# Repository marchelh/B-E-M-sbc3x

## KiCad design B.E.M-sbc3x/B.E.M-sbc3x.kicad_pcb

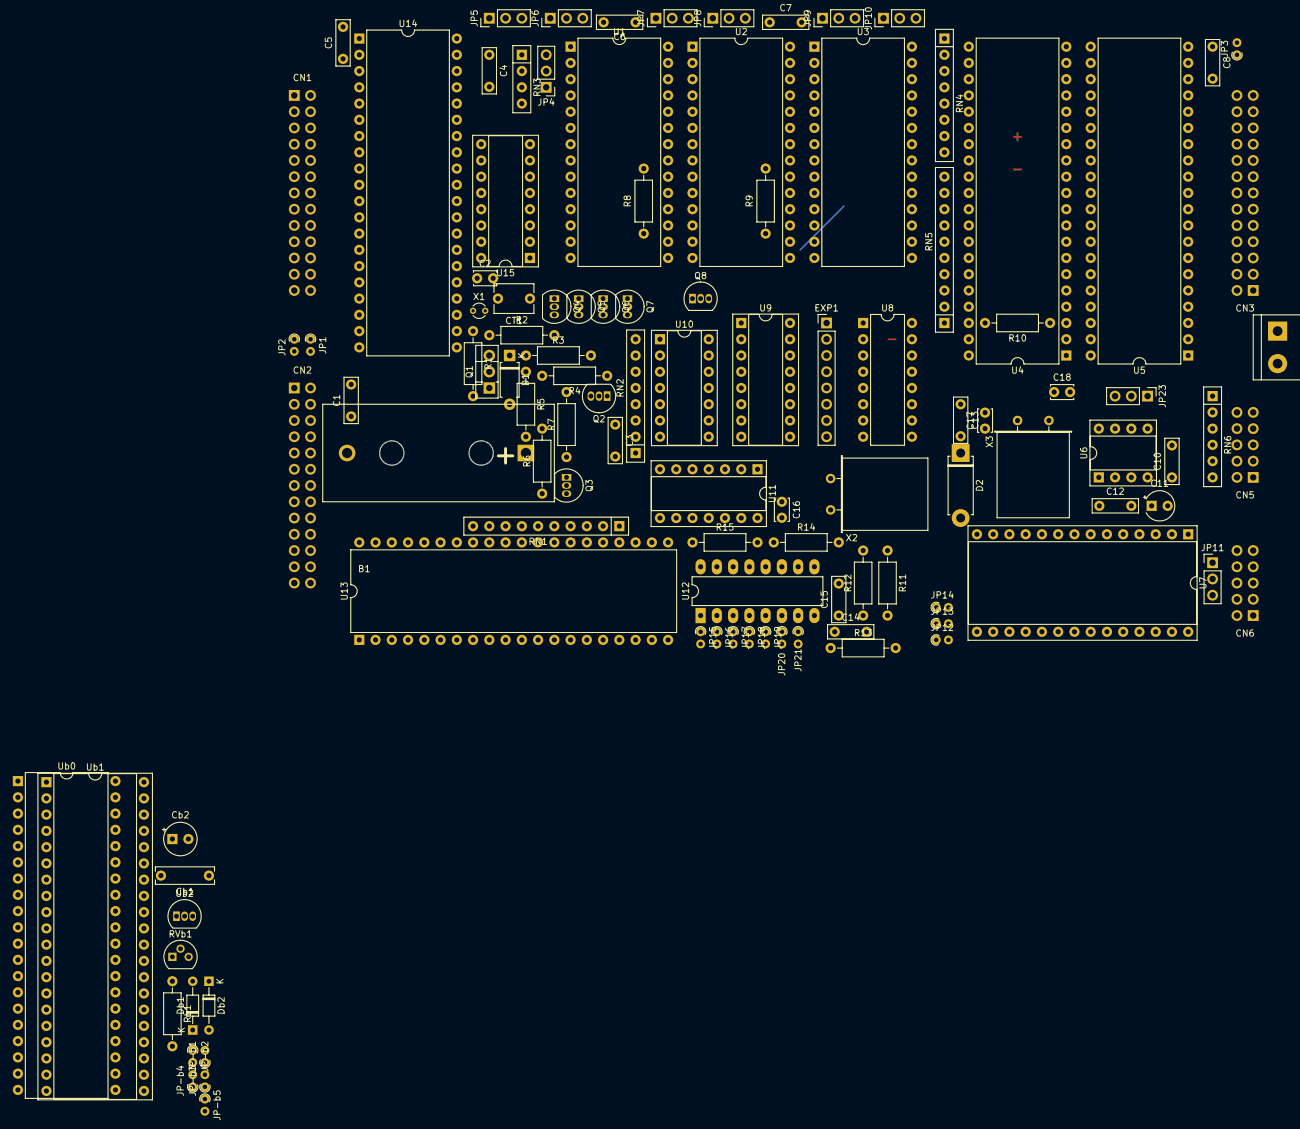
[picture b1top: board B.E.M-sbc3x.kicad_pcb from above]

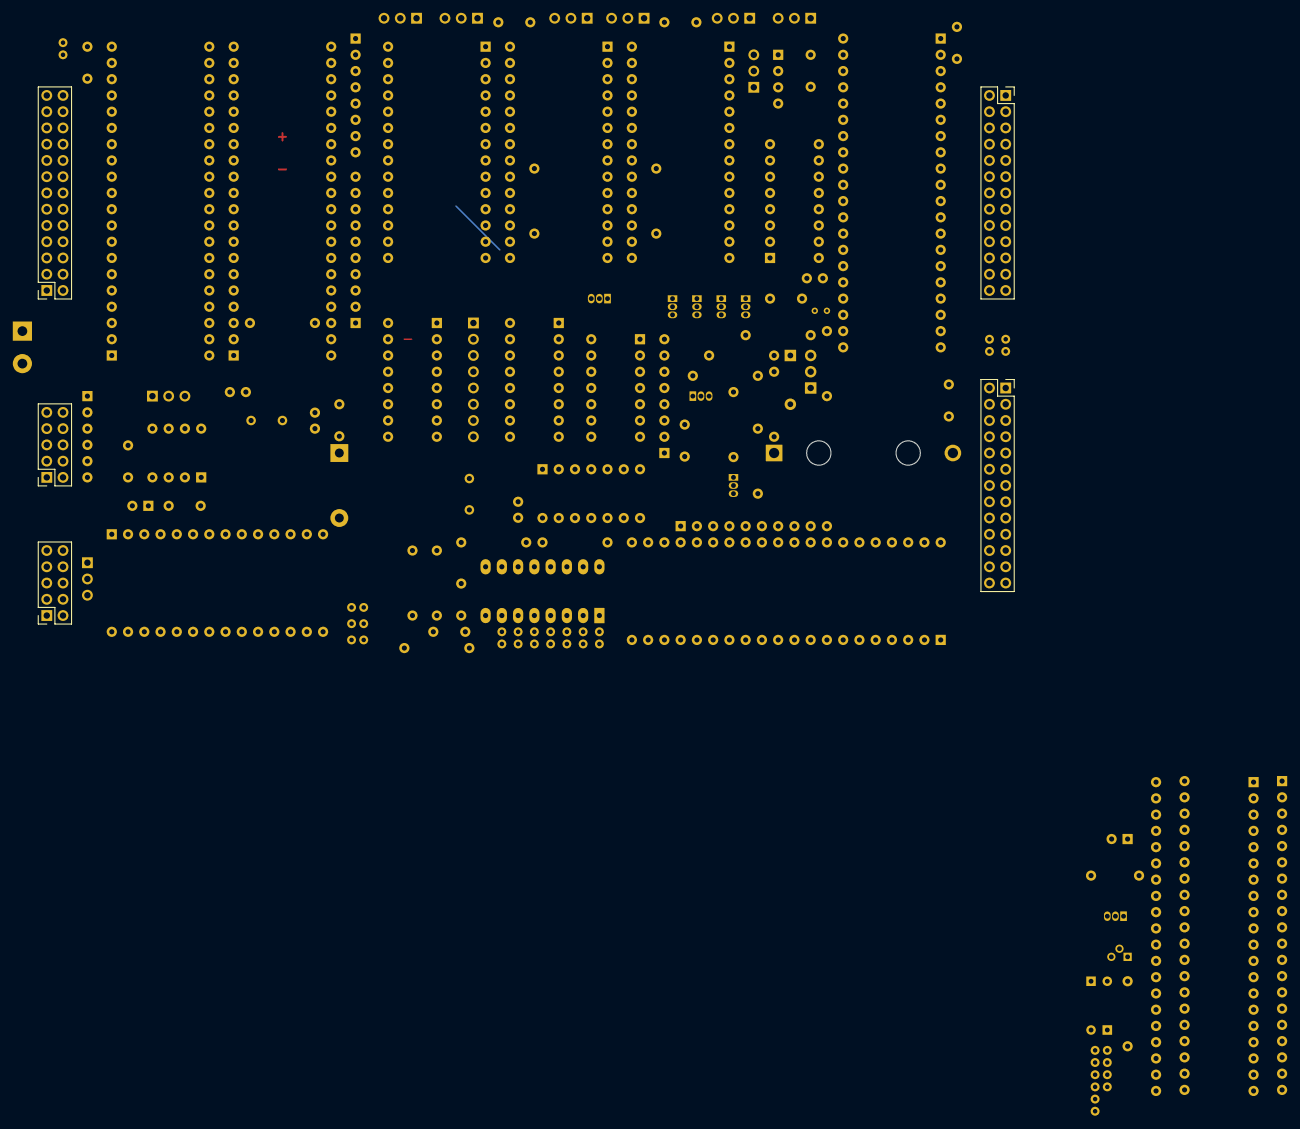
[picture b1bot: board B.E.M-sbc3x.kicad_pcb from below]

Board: 2 copper layers, 111 parts (5 on the bottom side), 206 nets.

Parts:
B1: Battery_Cell; Battery_3.6v
C1, C3, C4, C5, C6, C7, C8, C10, C12, C13, C14, C15: 100nF; C_Rect_L7.0mm_W2.0mm_P5.00mm
C2, C17, C18: 22pF; C_Disc_D3.4mm_W2.1mm_P2.50mm
C11: 10uF; CP_Radial_Tantal_D4.5mm_P2.50mm
C16: 100pF; C_Disc_D3.4mm_W2.1mm_P2.50mm
CN1, CN2, CN3: Conn_02x13_Odd_Even; PinSocket_2x13_P2.54mm_Vertical
CN5, CN6: Conn_02x05_Odd_Even; PinSocket_2x05_P2.54mm_Vertical
CT1: 6-30pF; C_Disc_D6.0mm_W4.4mm_P5.00mm
Cb1: 100nF; C_Rect_L9.0mm_W2.5mm_P7.50mm_MKT
Cb2: 100pF; CP_Radial_Tantal_D5.0mm_P2.50mm
D1: 1N4148; D_A-405_P7.62mm_Horizontal
D2: 1N4148; D_5W_P10.16mm_Horizontal
Db1, Db2: 1n4148; D_DO-34_SOD68_P7.62mm_Horizontal
EXP1: Exp; PinHeader_1x08_P2.54mm_Vertical
J1: Screw_Terminal_01x02; TerminalBlock_bornier-2_P5.08mm
JP1, JP2, JP3, JP12, JP13, JP14, JP15, JP16, JP17, JP18, JP19, JP20, JP21: Jumper_NO_Small; R_Axial_DIN0204_L3.6mm_D1.6mm_P1.90mm_Vertical
JP4, JP5, JP6, JP7, JP8, JP9, JP10, JP11, JP23: Jumper_3_Open; PinHeader_1x03_P2.54mm_Vertical
JP-b1, JP-b2, JP-b3, JP-b4, JP-b5: Device_Jumper_NO_Small; R_Axial_DIN0204_L3.6mm_D1.6mm_P1.90mm_Vertical
Q1: BD136; TO-126-3_Vertical
Q2: BC556; TO-92_Inline
Q3, Q4, Q5, Q6, Q7, Q8: BC547; TO-92_Inline
R1, R3, R4, R13: 10K; R_Axial_DIN0207_L6.3mm_D2.5mm_P10.16mm_Horizontal
R2, R6, R7: 1K; R_Axial_DIN0207_L6.3mm_D2.5mm_P10.16mm_Horizontal
R5: 100; R_Axial_DIN0207_L6.3mm_D2.5mm_P10.16mm_Horizontal
R8, R9, R10, R14, R15: 3.3K; R_Axial_DIN0207_L6.3mm_D2.5mm_P10.16mm_Horizontal
R11: 220K; R_Axial_DIN0207_L6.3mm_D2.5mm_P10.16mm_Horizontal
R12: 22K; R_Axial_DIN0207_L6.3mm_D2.5mm_P10.16mm_Horizontal
RN1, RN5: 10K; R_Array_SIP10
RN2: 2k; R_Array_SIP8
RN3: 3.3K; R_Array_SIP4
RN4: 10K; R_Array_SIP8
RN6: 3.3K; R_Array_SIP6
RVb1: R_POT; TO-92
Rb1: 2.2K; R_Axial_DIN0207_L6.3mm_D2.5mm_P10.16mm_Horizontal
U1, U2: TC55257PL-12; DIP-28_W15.24mm
U3: 27256; DIP-28_W15.24mm
U4: MC68A09; DIP-40_W15.24mm
U5, U13, U14: 6822; DIP-40_W15.24mm
U6: TL7705ACPSR; DIP-8_W7.62mm_Socket
U7: INS2651; DIP-28_W15.24mm_Socket
U8: DM74S571; DIP-16_W7.62mm
U9: 74LS42; DIP-16_W7.62mm_Socket
U10: 74LS00; DIP-14_W7.62mm_Socket
U11: 74HC04; DIP-14_W7.62mm_Socket
U12: CD4060BCN; DIP-16_W7.62mm_LongPads
U15: MM58274BN; DIP-16_W7.62mm_Socket
Ub0: 6822; DIP-40_W15.24mm
Ub1: HD46508PA; DIP-40_W15.24mm_Socket
Ub2: LM336; TO-92_Inline
X1: 32.768; Crystal_DS26_D2.0mm_L6.0mm_Vertical
X2: 5.0688; Crystal_HC18-U_Horizontal
X3: 4.000; Crystal_HC18-U_Horizontal

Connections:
+5C: Cb1.1, Cb2.1, JP-b1.2, Rb1.2, Ub0.20, Ub1.20
+5V: C1.2, C3.2, C4.2, C5.2, C6.2, C7.2, C8.2, C10.2, C13.2, C14.2, CN1.1, CN2.1, CN3.1, EXP1.1, J1.1, JP5.3, JP6.3, JP8.3, JP11.2, JP11.3, Q1.1, R7.2, R8.1, R13.1, RN6.1, U3.1, U3.28, U4.7, U4.33, U5.20, U5.24, U6.7, U6.8, U7.26, U8.16, U9.16, U12.16, U13.20, U13.24, U14.20, U14.24
/A0: RN5.6, U1.10, U2.10, U3.10, U4.8, U5.38, U7.12, U13.38, U14.38, U15.12
/A1: RN5.7, U1.9, U2.9, U3.9, U4.9, U5.37, U7.10, U13.37, U14.37, U15.11
/A2: RN5.8, U1.8, U2.8, U3.8, U4.10, U5.36, U13.36, U14.36, U15.10
/A3: RN5.9, U1.7, U2.7, U3.7, U4.11, U5.35, U13.35, U14.35, U15.9
/A4: RN5.10, U1.6, U2.6, U3.6, U4.12
/A5: RN4.8, U1.5, U2.5, U3.5, U4.13
/A6: RN4.7, U1.4, U2.4, U3.4, U4.14
/A7: RN4.5, U1.3, U2.3, U3.3, U4.15
/A8: RN4.6, U1.25, U2.25, U3.25, U4.16, U8.6
/A9: RN4.4, U1.24, U2.24, U3.24, U4.17, U8.7
/A10: RN4.2, RN5.5, U1.21, U2.21, U3.21, U4.18, U8.4
/A11: JP4.1, JP4.2, JP6.1, JP8.1, U1.23, U2.23, U3.23, U4.19, U8.3
/A12: RN4.3, U1.2, U2.2, U3.2, U4.20, U8.2
/A13: RN5.2, U1.26, U4.21, U8.1
/A14: JP10.3, RN5.3, U4.22, U8.15
/A15: U4.23, U8.14
/C1-2: CN1.2, U14.40
/C1-3: CN1.3, U14.39
/C1-5: CN1.5, U14.2
/C1-6: CN1.6, U14.3
/C1-7: CN1.7, U14.4
/C1-8: CN1.8, U14.5
/C1-9: CN1.9, U14.6
/C1-10: CN1.10, U14.7
/C1-11: CN1.11, U14.8
/C1-15: CN1.15, U14.10
/C1-16: CN1.16, U14.11
/C1-17: CN1.17, U14.12
/C1-18: CN1.18, U14.13
/C1-19: CN1.19, U14.14
/C1-20: CN1.20, U14.15
/C1-21: CN1.21, U14.16
/C1-22: CN1.22, U14.17
/C1-23: CN1.23, JP1.1
/C1-24: CN1.24, U14.18
/C1-25: CN1.25, U14.19
/C2-2: CN2.2, U13.40
/C2-3: CN2.3, JP19.1, U5.39, U13.39
/C2-5: CN2.5, U13.2
/C2-6: CN2.6, U13.3
/C2-7: CN2.7, U13.4
/C2-8: CN2.8, U13.5
/C2-9: CN2.9, U13.6
/C2-10: CN2.10, U13.7
/C2-11: CN2.11, U13.8
/C2-15: CN2.15, U13.10
/C2-16: CN2.16, U13.11
/C2-17: CN2.17, U13.12
/C2-18: CN2.18, U13.13
/C2-19: CN2.19, U13.14
/C2-20: CN2.20, U13.15
/C2-21: CN2.21, U13.16
/C2-22: CN2.22, U13.17
/C2-23: CN2.23, JP2.1
/C2-24: CN2.24, U13.18
/C2-25: CN2.25, JP20.1, U13.19
/C3-2: CN3.2, U5.40
/C3-5: CN3.5, U5.2
/C3-6: CN3.6, U5.3
/C3-7: CN3.7, U5.4
/C3-8: CN3.8, U5.5
/C3-9: CN3.9, U5.6
/C3-10: CN3.10, U5.7
/C3-11: CN3.11, U5.8
/C3-15: CN3.15, U5.10
/C3-16: CN3.16, U5.11
/C3-17: CN3.17, U5.12
/C3-18: CN3.18, U5.13
/C3-19: CN3.19, U5.14
/C3-20: CN3.20, U5.15
/C3-21: CN3.21, U5.16
/C3-22: CN3.22, U5.17
/C3-23: CN3.23, JP3.1
/C3-24: CN3.24, U5.18
/C3-25: CN3.25, U5.19
/C5-1: CN5.1, RN6.6, U6.5
/C5-2: CN5.2, JP23.3, R10.1, U4.4
/C5-3: CN5.3, RN6.4, U4.2
/C5-4: CN5.4, JP1.2, JP2.2, JP3.2, JP23.1, RN6.5, U4.3, U5.21, U13.21, U14.21
/C5-5: CN5.5, RN6.3, U4.40
/C5-10: CN5.10, D2.2, RN6.2, U6.2
/D0: RN1.10, U1.11, U2.11, U3.11, U4.31, U5.33, U7.27, U13.33, U14.33, U15.7
/D1: RN1.9, U1.12, U2.12, U3.12, U4.30, U5.32, U7.28, U13.32, U14.32, U15.6
/D2: RN1.8, U1.13, U2.13, U3.13, U4.29, U5.31, U7.1, U13.31, U14.31, U15.5
/D3: RN1.7, U1.15, U2.15, U3.15, U4.28, U5.30, U7.2, U13.30, U14.30, U15.4
/D4: RN1.6, U1.16, U2.16, U3.16, U4.27, U5.29, U7.5, U13.29, U14.29
/D5: RN1.5, U1.17, U2.17, U3.17, U4.26, U5.28, U7.6, U13.28, U14.28
/D6: RN1.4, U1.18, U2.18, U3.18, U4.25, U5.27, U7.7, U13.27, U14.27
/D7: RN1.3, U1.19, U2.19, U3.19, U4.24, U5.26, U7.8, U13.26, U14.26
/DATAC-1A/D0: Ub0.33, Ub1.4
/DATAC-1A/D1: Ub0.32, Ub1.5
/DATAC-1A/D2: Ub0.31, Ub1.6
/DATAC-1A/D3: Ub0.30, Ub1.7
/DATAC-1A/D4: Ub0.29, Ub1.8
/DATAC-1A/D5: Ub0.28, Ub1.9
/DATAC-1A/D6: Ub0.27, Ub1.10
/DATAC-1A/D7: Ub0.26, Ub1.11
/DATAC-1A/PA0: Ub0.2, Ub1.40
/DATAC-1A/PA1: Ub0.3, Ub1.39
/DATAC-1A/PA2: Ub0.4, Ub1.38
/DATAC-1A/PA3: Ub0.5, Ub1.37
/DATAC-1A/PA4: Ub0.6, Ub1.36
/DATAC-1A/PA5: Ub0.7, Ub1.35
/DATAC-1A/PA6: Ub0.8, Ub1.34
/DATAC-1A/PA7: Ub0.9, Ub1.33
/E: U4.34, U5.25, U10.4, U10.10, U13.25, U14.25
/RW: U4.32, U5.22, U7.13, U11.5, U13.22, U14.22
/Reset: U4.37, U5.34, U10.13, U11.9, U13.34, U14.34
BrC: C16.2, EXP1.7, R14.1, U7.20, U11.12
GND: B1.2, C1.1, C3.1, C4.1, C5.1, C6.1, C7.1, C8.1, C10.1, C11.2, C12.2, C13.1, C14.1, C17.2, C18.2, CN1.12, CN1.13, CN2.12, CN2.13, CN3.12, CN3.13, EXP1.8, J1.2, JP18.2, Q3.3, R6.1, RN1.1, RN4.1, RN5.1, U1.14, U2.14, U3.14, U4.1, U5.1, U5.9, U6.4, U7.4, U8.8, U8.13, U9.8, U11.1, U12.8, U13.1, U13.9, U14.1, U14.9, U15.8
GNDA: Cb1.2, Cb2.2, Db2.1, JP-b5.2, Ub0.1, Ub1.1, Ub2.3
unnamed: B1.1, R5.2
unnamed: C2.1, CT1.1
unnamed: C2.2, U15.14, X1.1
unnamed: C11.1, U6.3
unnamed: C12.1, U6.1
unnamed: C15.1, R11.2, R12.1
unnamed: C15.2, U12.9
unnamed: C16.1, R15.2, U11.11
unnamed: C17.1, U4.38, X3.1
unnamed: C18.1, U4.39, X3.2
unnamed: CT1.2, U15.15, X1.2
unnamed: D1.1, JP5.1, R1.2, R3.1, RN3.1
unnamed: D1.2, R5.1
unnamed: D2.1, U11.2
unnamed: Db1.1, JP-b2.1, RVb1.1
unnamed: Db1.2, Ub2.2
unnamed: Db2.2, RVb1.3
unnamed: EXP1.2, U8.12, U9.15
unnamed: EXP1.3, U8.11, U9.14
unnamed: EXP1.4, U8.10, U9.13
unnamed: EXP1.5, U8.9, U9.12
unnamed: EXP1.6, U9.3
unnamed: JP4.3, Q5.3, Q6.3, U1.27, U2.27, U10.6
unnamed: JP5.2, U15.16
unnamed: JP6.2, U1.1, U1.28
unnamed: JP7.2, U2.1
unnamed: JP7.3, JP8.2, JP9.1, U2.28
unnamed: JP9.2, U2.26
unnamed: JP9.3, U3.26
unnamed: JP7.1, JP10.1
unnamed: JP10.2, U3.27
unnamed: JP11.1, U7.22
unnamed: JP12.1, JP13.1, JP14.1, JP23.2
unnamed: JP12.2, U7.15
unnamed: JP13.2, U7.14
unnamed: JP14.2, U7.18
unnamed: JP15.1, U12.1
unnamed: JP15.2, JP16.2, JP17.2, JP18.1
unnamed: JP16.1, U12.2
unnamed: JP17.1, U12.3
unnamed: JP19.2, JP20.2, JP21.2, R13.2, U12.12
unnamed: JP21.1, U10.11
unnamed: JP-b1.1, JP-b2.2, Ub1.24
unnamed: JP-b3.1, Ub0.19
unnamed: JP-b3.2, Ub0.18
unnamed: JP-b4.1, Ub1.22
unnamed: JP-b4.2, Ub1.23
unnamed: JP-b5.1, Ub1.21
unnamed: Q1.2, Q2.3, R9.1
unnamed: Q1.3, R1.1, R2.1
unnamed: Q2.1, RN2.1
unnamed: Q2.2, R3.2, R4.1
unnamed: Q3.1, R2.2, R4.2
unnamed: Q3.2, R6.2
unnamed: Q4.1, RN3.4, U15.1
unnamed: Q4.2, RN2.5
unnamed: Q4.3, U9.10
unnamed: Q5.1, RN3.3, U15.2
unnamed: Q5.2, RN2.6
unnamed: Q6.1, RN3.2, U15.3
unnamed: Q6.2, RN2.7
unnamed: Q7.1, U9.1
unnamed: Q7.2, RN2.8
unnamed: Q7.3, R8.2, U1.20
unnamed: Q8.1, U9.2
unnamed: Q8.2, RN2.2
unnamed: Q8.3, R9.2, U2.20
unnamed: R10.2, U4.36
unnamed: R11.1, U12.11
unnamed: R12.2, U12.10
unnamed: R14.2, U11.13, X2.1
unnamed: R15.1, U11.10, X2.2
unnamed: RVb1.2, Rb1.1, Ub2.1
unnamed: U1.22, U2.22, U10.5, U11.6
unnamed: U3.20, U9.11
unnamed: U5.23, U9.6
unnamed: U10.1, U10.2
unnamed: U7.11, U10.8
unnamed: U10.9, U11.4
unnamed: U7.19, U10.12
unnamed: U9.7, U11.3
unnamed: U7.21, U11.8
unnamed: U9.5, U13.23
unnamed: U9.4, U14.23
unnamed: Ub0.21, Ub1.3
unnamed: Ub0.22, Ub1.18
unnamed: Ub0.23, Ub1.17
unnamed: Ub0.24, Ub1.16
unnamed: Ub0.25, Ub1.12, Ub1.13
unnamed: Ub0.34, Ub1.19
unnamed: Ub0.37, Ub1.15
unnamed: Ub0.38, Ub1.14
unnamed: Ub0.39, Ub1.2

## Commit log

2019-12-08 Initial start of the project
2019-12-31 Almost finnished with the schema and layout. Only some jumpers are not yet mapped out. For the PCB layout is only component placement is done, no routing
2020-01-02 All connectors are mapped, daughter DATAC-1A mapped, components all placed on PCB, HD46508PA added to library
2020-01-02 all support files for KiCAD
